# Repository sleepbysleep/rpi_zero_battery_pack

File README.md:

# rpi_zero_battery_pack
Battery, and power management platform for Raspberry Pi (zero) inspired by LiPoPi.
Please refer https://github.com/NeonHorizon/lipopi
This includes KiCad files with schematic, PCB, and 3D View.

# circuit

<object data="./rpi_zero_battery_pack.sch.pdf" type="application/pdf" width="700px" height="700px">
    <embed src="./rpi_zero_battery_pack.sch.pdf">
        <p>This browser does not support PDFs. Please download the PDF to view it: <a href="./rpi_zero_battery_pack.sch.pdf">Download PDF</a>.</p>
    </embed>
</object>

# pcb

# 3d view

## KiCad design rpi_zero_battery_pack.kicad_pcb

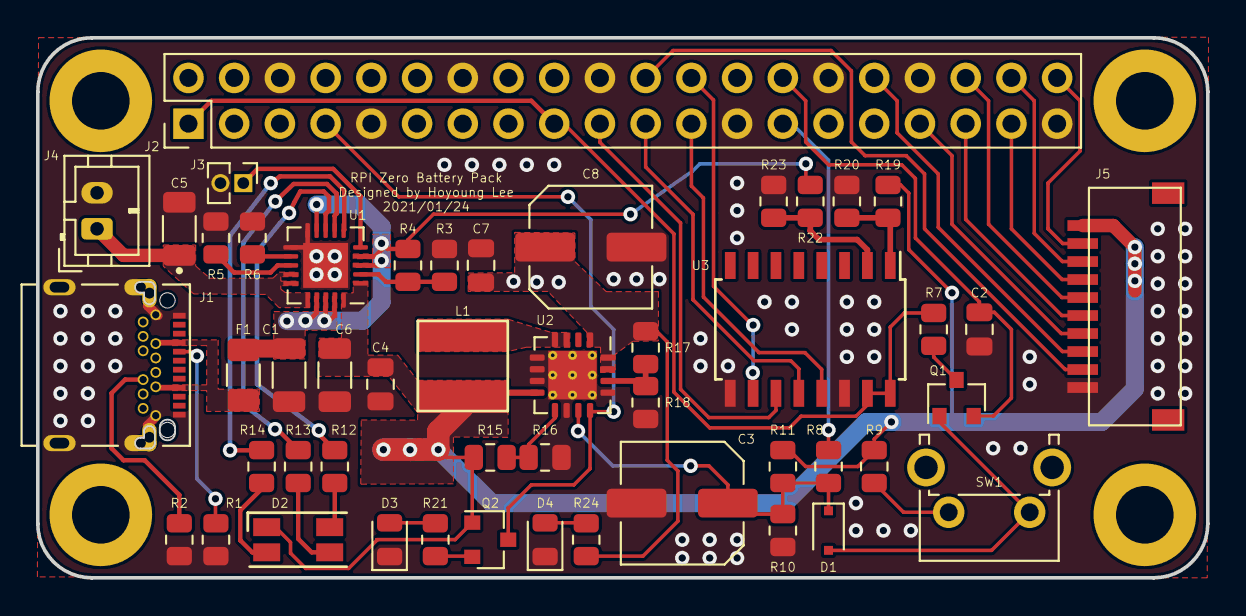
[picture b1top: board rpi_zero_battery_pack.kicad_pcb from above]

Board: 2 copper layers, 65.0 x 30.0 mm, 49 parts (0 on the bottom side), 46 nets.

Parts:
C1, C5, C6: 10uF/10V; C_1206_3216Metric
C2: 0.1uF; C_0805_2012Metric
C3: 100uF/10V; C_Elec_6.3x5.4
C4: 100nF; C_0805_2012Metric
C7: 2.2uF; C_0805_2012Metric
C8: 100uF; C_Elec_6.3x5.4
D1: BAT54J; D_SOD-323F
D2: BATT_STATUS; LED_RGB_1210
D3: LOW_BATT; LED_0805_2012Metric
D4: PWR; LED_0805_2012Metric
F1: 1206L300SLTHYR; Fuse_1206_3216Metric
J1: UJ31-CH-3-SMT-TR; CUI_UJ31-CH-3-SMT-TR
J2: Raspberry_Pi_2_3; PinHeader_2x20_P2.54mm_Vertical
J3: 10K(NTC); PinHeader_1x02_P1.27mm_Vertical
J4: LIPO(1S1P); JST_PH_B2B-PH-K_1x02_P2.00mm_Vertical
J5: Conn_01x10; JST_10FMN-SMT-A-TF(LF)(SN)_1x10-1MP_P1.00mm_Horizontal
L1: 6.8uH; L_Laird_TYS5040470M-10
Q1: MMBT3904; SOT-23
Q2: MMUN2133LT1G; SOT-23
R1, R2: 5.1K; R_0805_2012Metric
R3, R6, R10: 100K; R_0805_2012Metric
R4: 270K; R_0805_2012Metric
R5: 1.0K; R_0805_2012Metric
R7, R8, R9, R20, R23: 10K; R_0805_2012Metric
R11, R18: 200K; R_0805_2012Metric
R12, R13, R14, R21, R24: 1K; R_0805_2012Metric
R15, R17: 1.87M; R_0805_2012Metric
R16: 340K; R_0805_2012Metric
R19, R22: 6.8K; R_0805_2012Metric
SW1: SW_Push; SW_Tactile_SPST_Angled_PTS645Vx39-2LFS
U1: MCP73871-2CC; QFN-20-1EP_4x4mm_P0.5mm_EP2.5x2.5mm
U2: TPS61090; Texas_S-PVQFN-N16_EP2.7x2.7mm_ThermalVias
U3: MCP3008; SOIC-16W_5.3x10.2mm_P1.27mm

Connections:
+3V3: J2.1, J2.17, R7.2, U3.15, U3.16
+5V: C7.1, C8.1, J2.2, J2.4, R17.1, R24.1, U2.1, U2.15, U2.16
+BATT: C4.2, C6.1, D2.1, J5.1, L1.1, Q2.1, R9.2, R11.1, R15.1, R19.1, U1.1, U1.20, U2.8
/CE0: J2.24, U3.10
/CHRG: R12.2, U1.8
/DONE: R13.2, U1.7
/LBO: J2.7, Q2.3, U2.12
/LED0: J2.40, J5.2
/LED1: J2.38, J5.3
/LED2: J2.37, J5.4
/LED3: J2.36, J5.5
/LED4: J2.35, J5.6
/LED5: J2.33, J5.7
/LED6: J2.32, J5.8
/LED7: J2.22, J5.9
/MISO0: J2.21, U3.12
/MOSI0: J2.19, U3.11
/PWR_EN: C3.1, D1.1, R8.1, R10.1, R11.2, U2.11
/PWR_PIN: J2.27, R8.2
/PWR_SENSE: C2.1, J2.28, Q1.2
/SCLK0: J2.23, U3.13
/USB: R14.2, U1.6
/VLIPO: C5.1, J4.1, U1.14, U1.15, U1.16
GND: C1.2, C2.2, C3.2, C4.1, C5.2, C6.2, C7.2, C8.2, D3.1, D4.1, J1.A1, J1.A12, J1.B1, J1.B12, J1.SH1, J1.SH2, J1.SH3, J1.SH4, J1.SH5, J1.SH6, J2.6, J2.9, J2.14, J2.20, J2.25, J2.30, J2.34, J2.39, J3.2, J4.2, J5.10, R1.1, R2.1, R3.1, R5.2, R6.2, R10.2, R16.2, R18.2, R20.2, R23.2, U1.10, U1.11, U1.21, U2.5, U2.6, U2.7, U2.10, U2.13, U2.17, U3.9, U3.14
unnamed: D1.2, Q1.1, SW1.1
unnamed: D2.2, R14.1
unnamed: D2.3, R13.1
unnamed: D2.4, R12.1
unnamed: D3.2, R21.2
unnamed: D4.2, R24.2
unnamed: F1.2, J1.A4, J1.A9, J1.B4, J1.B9
unnamed: J1.A5, R1.2
unnamed: J1.B5, R2.2
unnamed: J3.1, U1.5
unnamed: L1.2, U2.3, U2.4
unnamed: Q1.3, R7.1
unnamed: Q2.2, R21.1
unnamed: R3.2, R4.1, U1.2
unnamed: R5.1, U1.13
unnamed: R6.1, U1.12
unnamed: R9.1, SW1.2
unnamed: R15.2, R16.1, U2.9
unnamed: R17.2, R18.1, U2.14
unnamed: R19.2, R20.1, U3.1
unnamed: R22.2, R23.1, U3.2
VBUS: C1.1, F1.1, R4.2, R22.1, U1.3, U1.4, U1.9, U1.17, U1.18, U1.19
